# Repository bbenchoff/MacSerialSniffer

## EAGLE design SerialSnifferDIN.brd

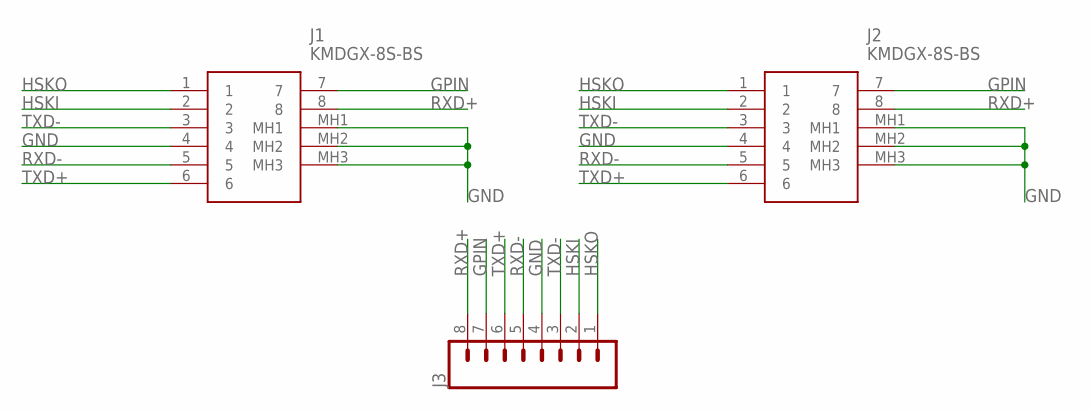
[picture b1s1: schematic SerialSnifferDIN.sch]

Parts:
J1, J2: KMDGX-8S-BS; KMDGX8SBS
J3: CONN_08LOCK_LONGPADS; 1X08_LOCK_LONGPADS

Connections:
GND: J1.4, J1.MH1, J1.MH2, J1.MH3, J2.4, J2.MH1, J2.MH2, J2.MH3, J3.4
GPIN: J1.7, J2.7, J3.7
HSKI: J1.2, J2.2, J3.2
HSKO: J1.1, J2.1, J3.1
RXD+: J1.8, J2.8, J3.8
RXD-: J1.5, J2.5, J3.5
TXD+: J1.6, J2.6, J3.6
TXD-: J1.3, J2.3, J3.3

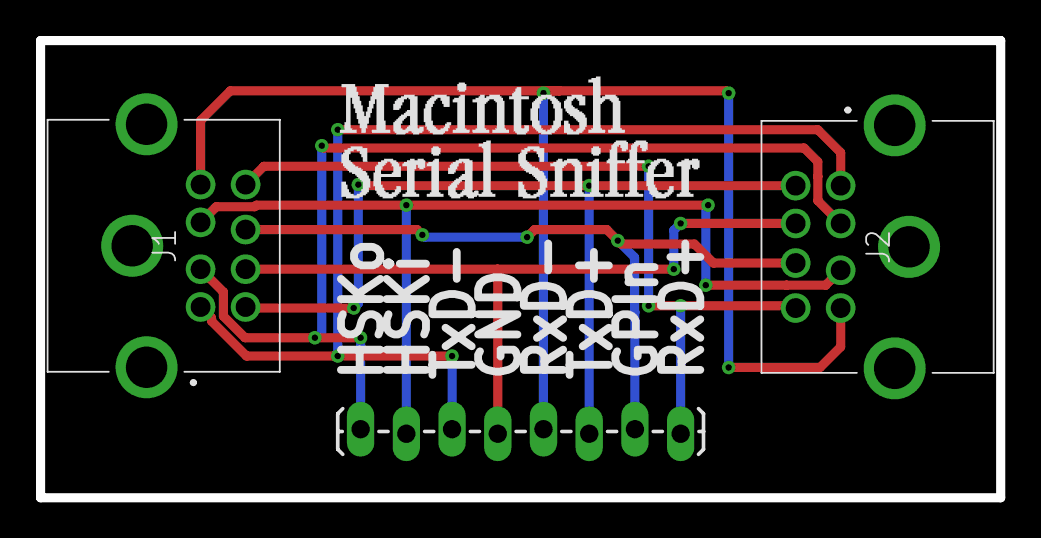
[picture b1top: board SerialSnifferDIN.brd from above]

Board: 2 copper layers, 53.3 x 25.4 mm, 3 parts (0 on the bottom side), 8 nets.

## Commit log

2022-06-29 initial sniffer

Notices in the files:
parts and their libraries:
SparkFun-Connectors: Licensing: Creative Commons ShareAlike 4.0 International - https://creativecommons.org/licenses/by-sa/4.0
